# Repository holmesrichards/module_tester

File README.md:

Eurorack module tester.

This project is a test signal generator for Eurorack synth modules. It also provides frequency/clock measurement tools, and a +/12V and +5V power supply - making it a compact "all in one" box for powering and debugging a module.

Original developer: Emilie Gillet (emilie.o.gillet@gmail.com)

Forked from pichenettes' version and identical except:
- Eagle brd and sch files converted to XML (making possible import into KiCad)

The firmware is released under a GPL3.0 license. The PCB layouts and schematics are released under a Creative Commons cc-by-sa 3.0 license.

To build code and flash a blank 644p:
make -f module_tester/makefile bootstrap

this is a test

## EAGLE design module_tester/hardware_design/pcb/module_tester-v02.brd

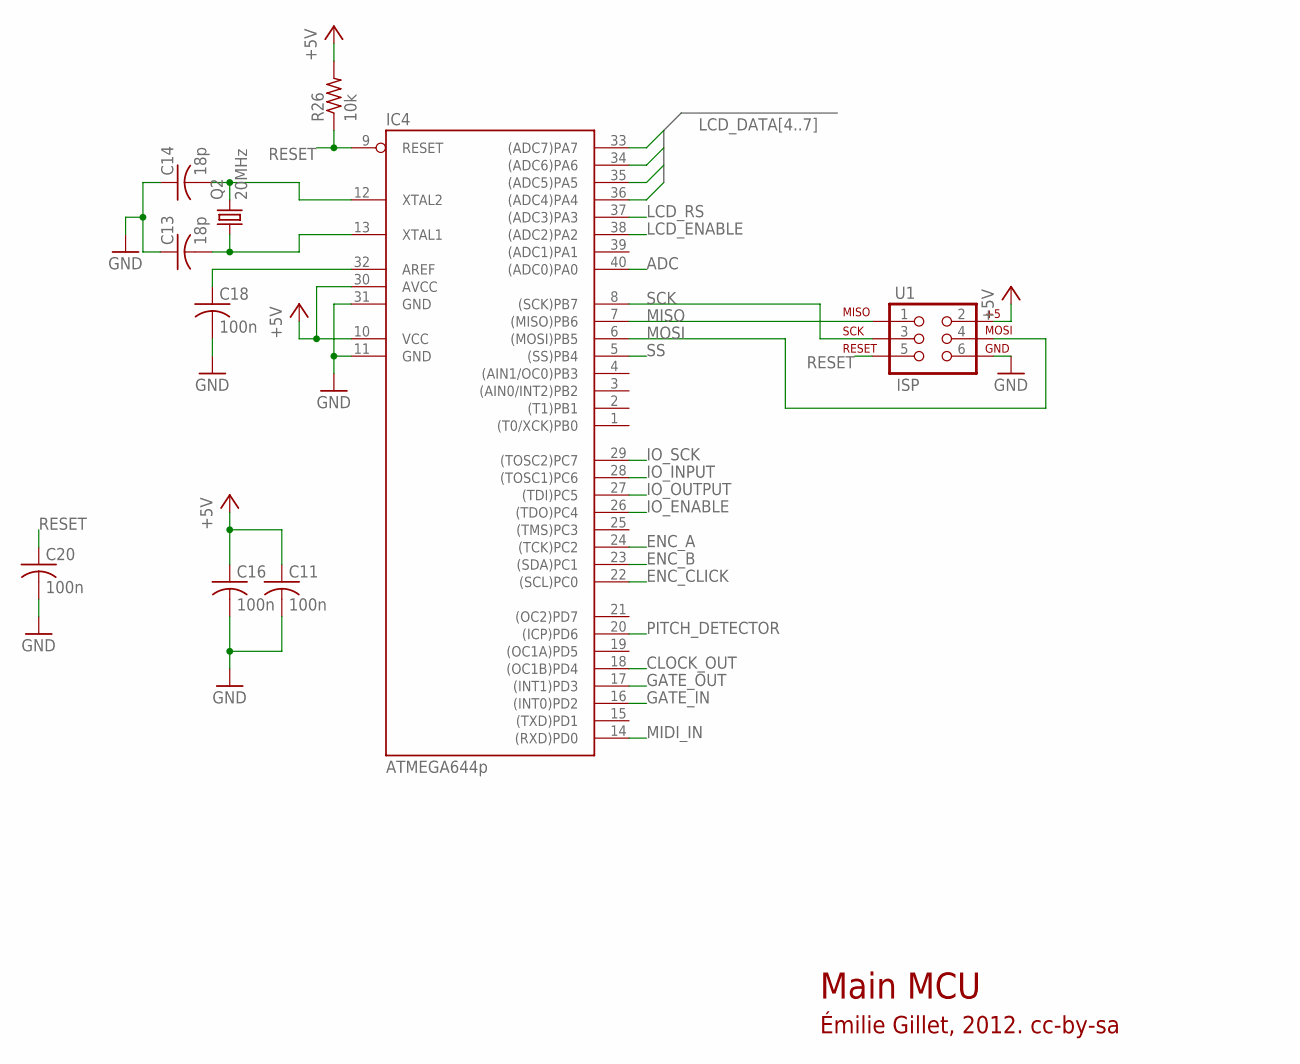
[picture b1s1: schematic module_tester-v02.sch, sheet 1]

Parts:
C11, C16, C18, C20: 100n; C025-025X050
C13, C14: 18p; C025-025X050
IC4: ATMEGA644p; DIL40
Q2: 20MHz; HC49U-V
R26: 10k; 0204/7
U1: ISP; 2X3

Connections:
+5V: C11.1, C16.1, IC4.10 (VCC), IC4.30 (AVCC), R26.2, U1.2; also elsewhere on the board
ADC: IC4.40 ((ADC0)PA0); also elsewhere on the board
CLOCK_OUT: IC4.18 ((OC1B)PD4); also elsewhere on the board
ENC_A: IC4.24 ((TCK)PC2); also elsewhere on the board
ENC_B: IC4.23 ((SDA)PC1); also elsewhere on the board
ENC_CLICK: IC4.22 ((SCL)PC0); also elsewhere on the board
GATE_IN: IC4.16 ((INT0)PD2); also elsewhere on the board
GATE_OUT: IC4.17 ((INT1)PD3); also elsewhere on the board
GND: C11.2, C13.1, C14.1, C16.2, C18.2, C20.2, IC4.11 (GND), IC4.31 (GND), U1.6; also elsewhere on the board
IO_ENABLE: IC4.26 ((TDO)PC4); also elsewhere on the board
IO_INPUT: IC4.28 ((TOSC1)PC6); also elsewhere on the board
IO_OUTPUT: IC4.27 ((TDI)PC5); also elsewhere on the board
IO_SCK: IC4.29 ((TOSC2)PC7); also elsewhere on the board
LCD_DATA4: IC4.36 ((ADC4)PA4); also elsewhere on the board
LCD_DATA5: IC4.35 ((ADC5)PA5); also elsewhere on the board
LCD_DATA6: IC4.34 ((ADC6)PA6); also elsewhere on the board
LCD_DATA7: IC4.33 ((ADC7)PA7); also elsewhere on the board
LCD_ENABLE: IC4.38 ((ADC2)PA2); also elsewhere on the board
LCD_RS: IC4.37 ((ADC3)PA3); also elsewhere on the board
MIDI_IN: IC4.14 ((RXD)PD0); also elsewhere on the board
MISO: IC4.7 ((MISO)PB6), U1.1
MOSI: IC4.6 ((MOSI)PB5), U1.4; also elsewhere on the board
unnamed: C18.1, IC4.32 (AREF)
unnamed: C13.2, IC4.13 (XTAL1), Q2.1
unnamed: C14.2, IC4.12 (XTAL2), Q2.2
PITCH_DETECTOR: IC4.20 ((ICP)PD6); also elsewhere on the board
RESET: C20.1, IC4.9 (RESET), R26.1, U1.5
SCK: IC4.8 ((SCK)PB7), U1.3; also elsewhere on the board
SS: IC4.5 ((SS)PB4); also elsewhere on the board

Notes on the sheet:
Main MCU
Émilie Gillet, 2012. cc-by-sa

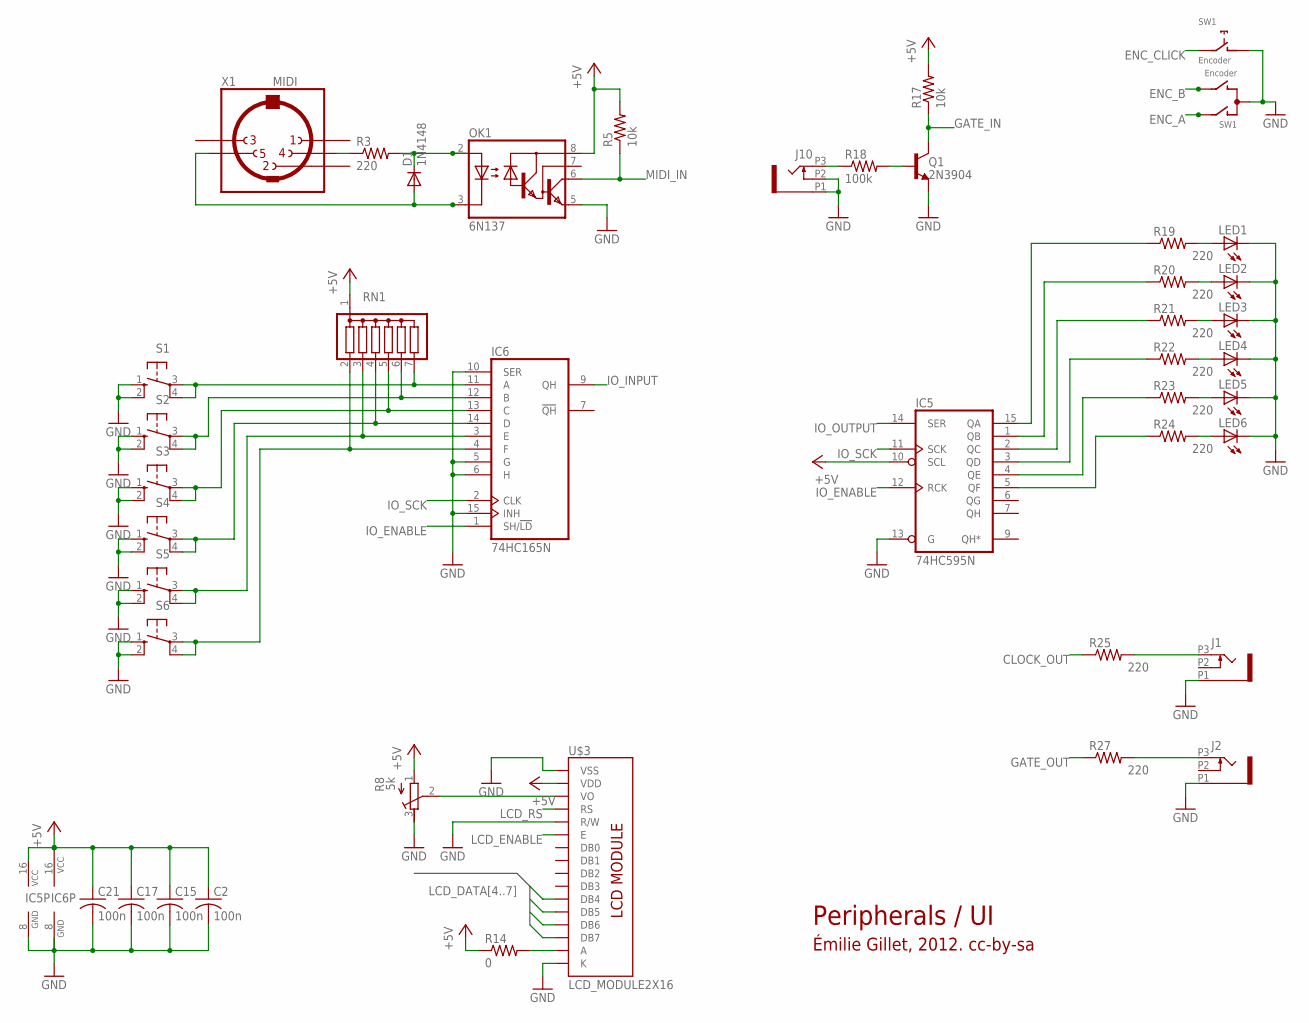
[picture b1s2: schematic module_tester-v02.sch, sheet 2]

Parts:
C2, C15, C17, C21: 100n; C025-025X050
D1: 1N4148; D-5
IC5: 74HC595N; DIL16
IC6: 74HC165N; DIL16
J1, J2, J10: PJ301_THONKICONN6; WQP_PJ_301M6
LED1, LED2, LED3, LED4, LED5, LED6: LED3MM
OK1: 6N137; DIL08
Q1: 2N3904; TO92-
R3, R19, R20, R21, R22, R23, R24, R25, R27: 220; 0204/7
R5, R17: 10k; 0204/7
R8: 5k; RTRIM3339P
R14: 0; 0204/7
R18: 100k; 0204/7
RN1: G06R; SIL7
S1, S2, S3, S4, S5, S6: 40-XX; B3F-40XX
SW1: Encoder; ALPS_EC12E_SW
U$3: LCD_MODULE2X16; LCD_MODULE_2X16
X1: MIDI; MAB5SH

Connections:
+5V: C2.1, C15.1, C17.1, C21.1, IC5.10 (SCL), IC5.16 (VCC), IC6.16 (VCC), OK1.8 (VCC), R5.2, R8.1 (E), R14.1, R17.2, RN1.1, U$3.2 (VDD); also elsewhere on the board
CLOCK_OUT: R25.1; also elsewhere on the board
ENC_A: SW1.A; also elsewhere on the board
ENC_B: SW1.B; also elsewhere on the board
ENC_CLICK: SW1.E (2); also elsewhere on the board
GATE_IN: Q1.1 (C), R17.1; also elsewhere on the board
GATE_OUT: R27.1; also elsewhere on the board
GND: C2.2, C15.2, C17.2, C21.2, IC5.8 (GND), IC5.13 (G), IC6.5 (G), IC6.6 (H), IC6.8 (GND), IC6.10 (SER), IC6.15 (INH), J1.P1 (1), J2.P1 (1), J10.P1 (1), J10.P2 (2), LED1.K (C), LED2.K (C), LED3.K (C), LED4.K (C), LED5.K (C), LED6.K (C), OK1.5 (GND), Q1.3 (E), R8.3 (A), S1.1 (S), S1.2 (S1), S2.1 (S), S2.2 (S1), S3.1 (S), S3.2 (S1), S4.1 (S), S4.2 (S1), S5.1 (S), S5.2 (S1), S6.1 (S), S6.2 (S1), SW1.C, SW1.D (1), U$3.1 (VSS), U$3.5 (R/W), U$3.16 (K); also elsewhere on the board
IO_ENABLE: IC5.12 (RCK), IC6.1 (SH/!LD); also elsewhere on the board
IO_INPUT: IC6.9 (QH); also elsewhere on the board
IO_OUTPUT: IC5.14 (SER); also elsewhere on the board
IO_SCK: IC5.11 (SCK), IC6.2 (CLK); also elsewhere on the board
LCD_DATA4: U$3.11 (DB4); also elsewhere on the board
LCD_DATA5: U$3.12 (DB5); also elsewhere on the board
LCD_DATA6: U$3.13 (DB6); also elsewhere on the board
LCD_DATA7: U$3.14 (DB7); also elsewhere on the board
LCD_ENABLE: U$3.6 (E); also elsewhere on the board
LCD_RS: U$3.4 (RS); also elsewhere on the board
MIDI_IN: OK1.6 (VO), R5.1; also elsewhere on the board
unnamed: IC5.2 (QC), R21.1
unnamed: IC5.4 (QE), R23.1
unnamed: LED5.A, R23.2
unnamed: J10.P3 (3), R18.1
unnamed: IC6.3 (E), RN1.3, S5.3, S5.4 (P1)
unnamed: J1.P3 (3), R25.2
unnamed: IC6.4 (F), RN1.2, S6.3, S6.4 (P1)
unnamed: IC6.14 (D), RN1.4, S4.3, S4.4 (P1)
unnamed: J2.P3 (3), R27.2
unnamed: R8.2 (S), U$3.3 (VO)
unnamed: LED6.A, R24.2
unnamed: IC5.5 (QF), R24.1
unnamed: IC6.11 (A), RN1.7, S1.3, S1.4 (P1)
unnamed: D1.C, OK1.2 (A), R3.2
unnamed: IC5.15 (QA), R19.1
unnamed: IC5.1 (QB), R20.1
unnamed: IC5.3 (QD), R22.1
unnamed: LED1.A, R19.2
unnamed: LED2.A, R20.2
unnamed: LED3.A, R21.2
unnamed: LED4.A, R22.2
unnamed: Q1.2 (B), R18.2
unnamed: R3.1, X1.4
unnamed: D1.A, OK1.3 (C), X1.5
unnamed: R14.2, U$3.15 (A)
unnamed: IC6.12 (B), RN1.6, S2.3, S2.4 (P1)
unnamed: IC6.13 (C), RN1.5, S3.3, S3.4 (P1)

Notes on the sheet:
Peripherals / UI
Émilie Gillet, 2012. cc-by-sa

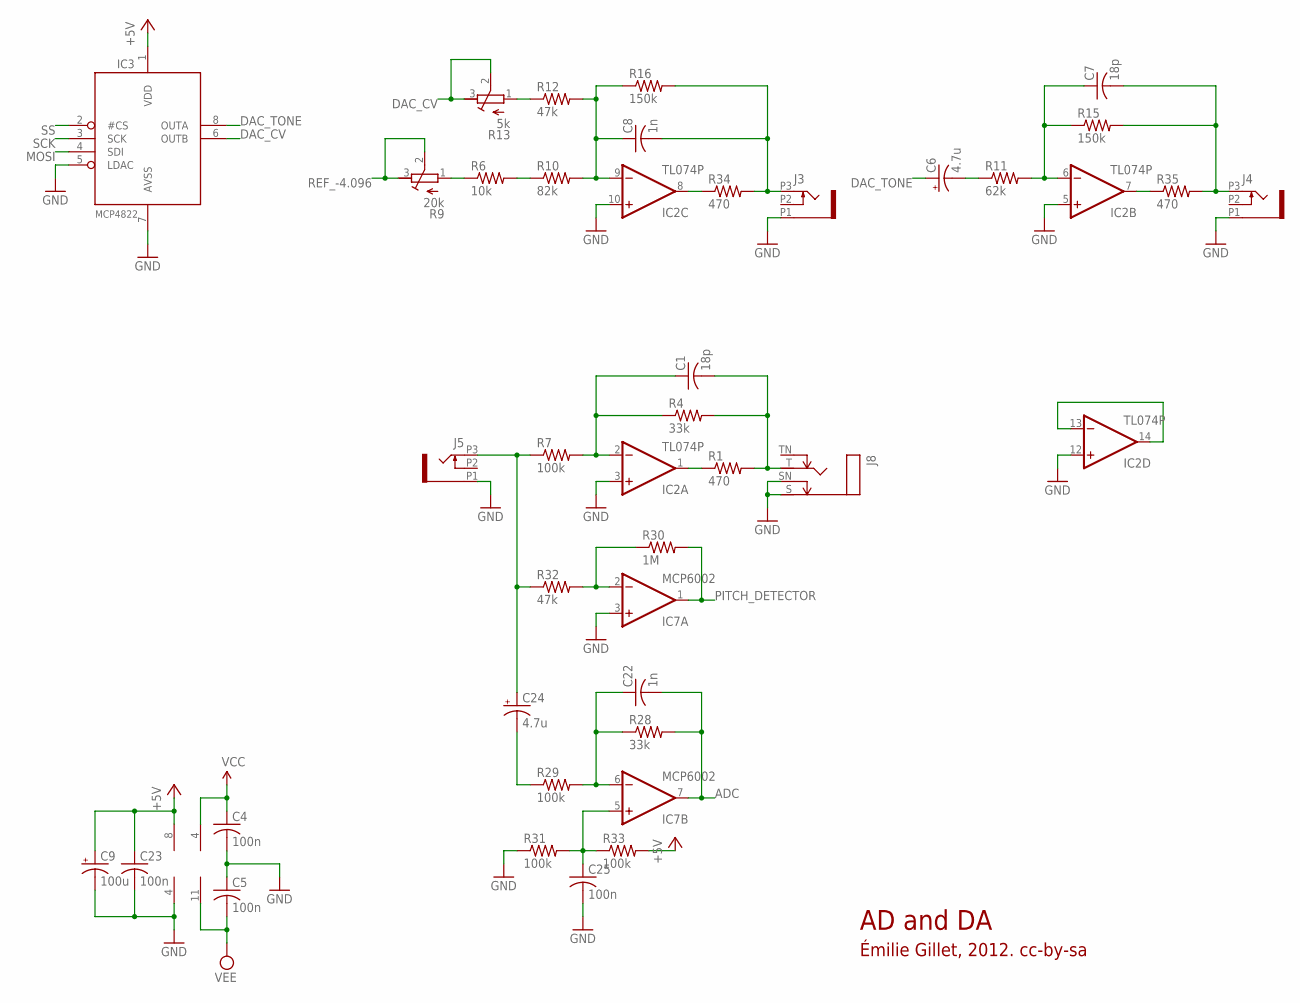
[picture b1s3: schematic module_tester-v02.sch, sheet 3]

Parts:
C1, C7: 18p; C025-025X050
C4, C5, C23, C25: 100n; C025-025X050
C6, C24: 4.7u; E2,5-6
C8, C22: 1n; C025-025X050
C9: 100u; E2,5-7
IC2: TL074P; DIL14
IC3: MCP4822; DIL08
IC7: MCP6002; DIL08
J3, J4, J5: PJ301_THONKICONN6; WQP_PJ_301M6
J8: MONOSWSLIM; NRJ4HF
R1, R34, R35: 470; 0204/7
R4, R28: 33k; 0204/7
R6: 10k; 0204/7
R7, R29, R31, R33: 100k; 0204/7
R9: 20k; RTRIM3296W
R10: 82k; 0204/7
R11: 62k; 0204/7
R12, R32: 47k; 0204/7
R13: 5k; RTRIM3296W
R15, R16: 150k; 0204/7
R30: 1M; 0204/7

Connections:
+5V: C9.+, C23.1, IC3.1 (VDD), IC7.8 (V+), R33.2; also elsewhere on the board
ADC: C22.2, IC7.7 (OUT), R28.2; also elsewhere on the board
DAC_CV: IC3.6 (OUTB), R13.2 (S), R13.3 (A)
DAC_TONE: C6.+, IC3.8 (OUTA)
GND: C4.2, C5.1, C9.-, C23.2, C25.2, IC2.3 (+IN), IC2.5 (+IN), IC2.10 (+IN), IC2.12 (+IN), IC3.5 (LDAC), IC3.7 (AVSS), IC7.3 (+IN), IC7.4 (V-), J3.P1 (1), J4.P1 (1), J5.P1 (1), J8.S, J8.SN, R31.1; also elsewhere on the board
MOSI: IC3.4 (SDI); also elsewhere on the board
unnamed: C24.+, J5.P3 (3), R7.1, R32.1
unnamed: IC2.8 (OUT), R34.1
unnamed: IC2.7 (OUT), R35.1
unnamed: C1.1, IC2.2 (-IN), R4.1, R7.2
unnamed: C1.2, J8.T, R1.2, R4.2
unnamed: C6.-, R11.1
unnamed: C7.1, IC2.6 (-IN), R11.2, R15.1
unnamed: C8.2, J3.P3 (3), R16.2, R34.2
unnamed: C8.1, IC2.9 (-IN), R10.2, R12.2, R16.1
unnamed: R12.1, R13.1 (E)
unnamed: R6.1, R9.1 (E)
unnamed: R6.2, R10.1
unnamed: C25.1, IC7.5 (+IN), R31.2, R33.1
unnamed: IC7.2 (-IN), R30.1, R32.2
unnamed: C22.1, IC7.6 (-IN), R28.1, R29.2
unnamed: C24.-, R29.1
unnamed: IC2.13 (-IN), IC2.14 (OUT)
unnamed: IC2.1 (OUT), R1.1
PITCH_DETECTOR: IC7.1 (OUT), R30.2; also elsewhere on the board
REF_-4.096: R9.2 (S), R9.3 (A); also elsewhere on the board
SCK: IC3.3 (SCK); also elsewhere on the board
SS: IC3.2 (#CS); also elsewhere on the board
TONE_OUT: C7.2, J4.P3 (3), R15.2, R35.2
VCC: C4.1, IC2.4 (V+); also elsewhere on the board
VEE: C5.2, IC2.11 (V-); also elsewhere on the board

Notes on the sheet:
AD and DA
Émilie Gillet, 2012. cc-by-sa

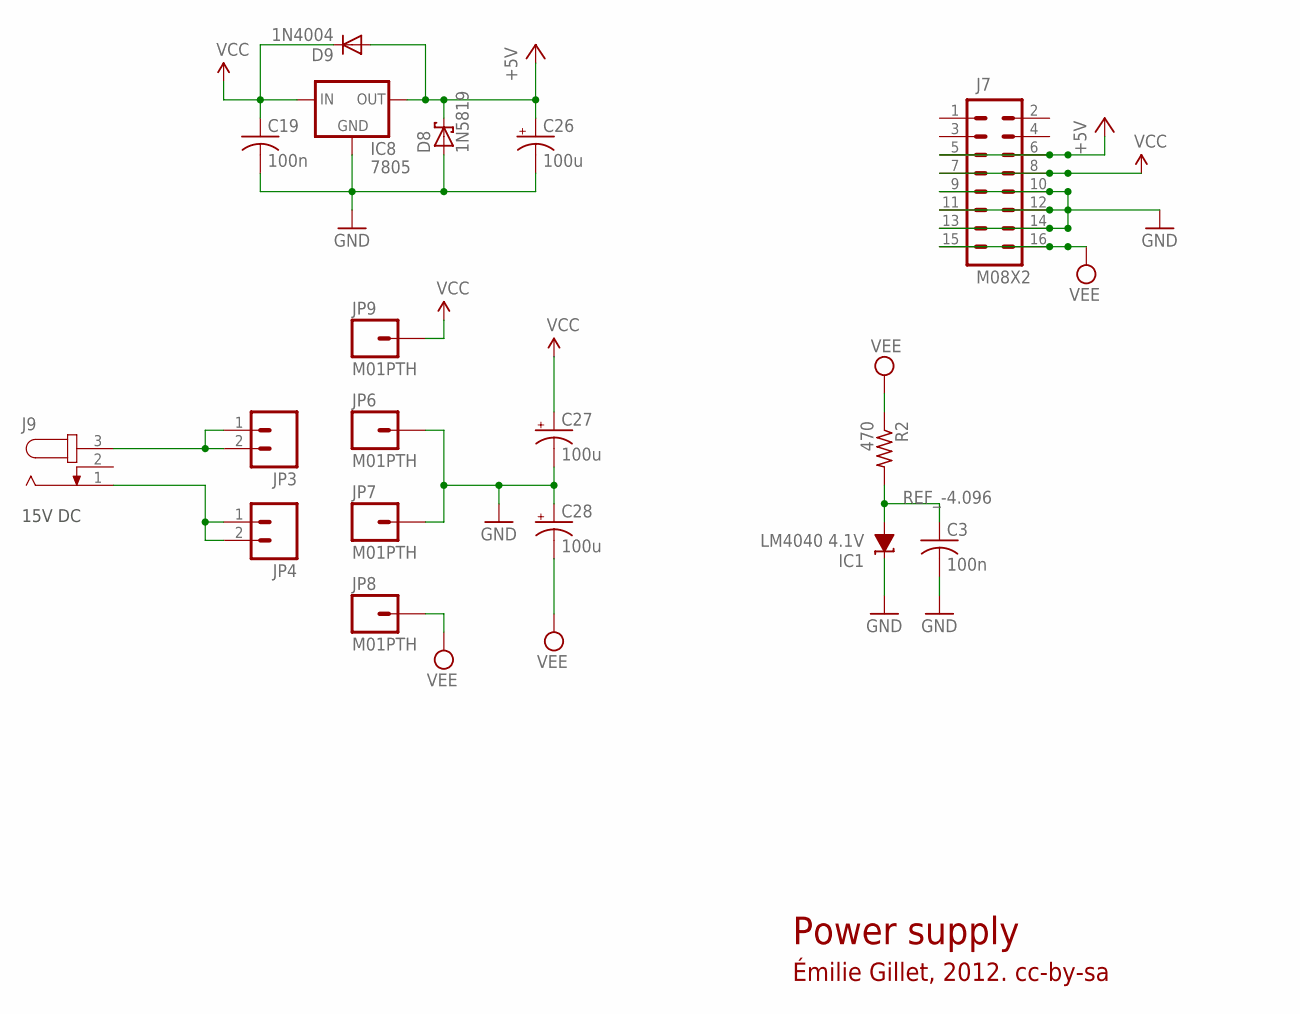
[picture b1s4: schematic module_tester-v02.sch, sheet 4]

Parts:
C3, C19: 100n; C025-025X050
C26, C27, C28: 100u; E2,5-7
D8: 1N5819; DO41-7.6
D9: 1N4004; DO41-10
IC1: LM4040 4.1V; LP_O-PBCY-W3
IC8: 7805; 78XXS
J7: M08X2; 2X8
J9: JACK-PLUG2; SPC4078_BIG_HOLES
JP3, JP4: M02PTH; 1X02
JP6, JP7, JP8, JP9: M01PTH; 1X01
R2: 470; 0204/7

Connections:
+5V: C26.+, D8.C, D9.A, IC8.OUT, J7.5, J7.6; also elsewhere on the board
GND: C3.2, C19.2, C26.-, C27.-, C28.+, D8.A, IC1.2 (C), IC8.GND, J7.9, J7.10, J7.11, J7.12, J7.13, J7.14, JP6.1, JP7.1; also elsewhere on the board
unnamed: J9.1, JP4.1, JP4.2
REF_-4.096: C3.1, IC1.3 (A), R2.2; also elsewhere on the board
TIP: J9.3, JP3.1, JP3.2
VCC: C19.1, C27.+, D9.C, IC8.IN, J7.7, J7.8, JP9.1; also elsewhere on the board
VEE: C28.-, J7.15, J7.16, JP8.1, R2.1; also elsewhere on the board

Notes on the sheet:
Power supply
Émilie Gillet, 2012. cc-by-sa
15V DC

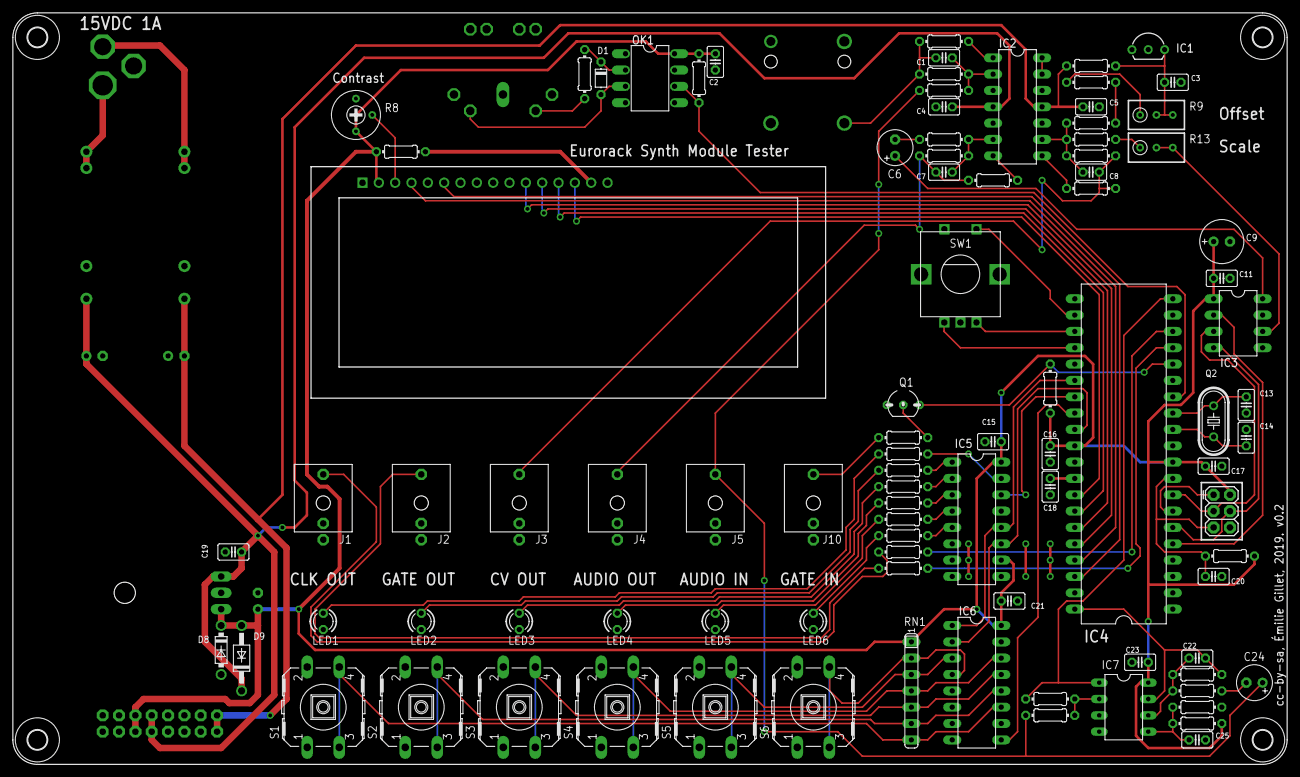
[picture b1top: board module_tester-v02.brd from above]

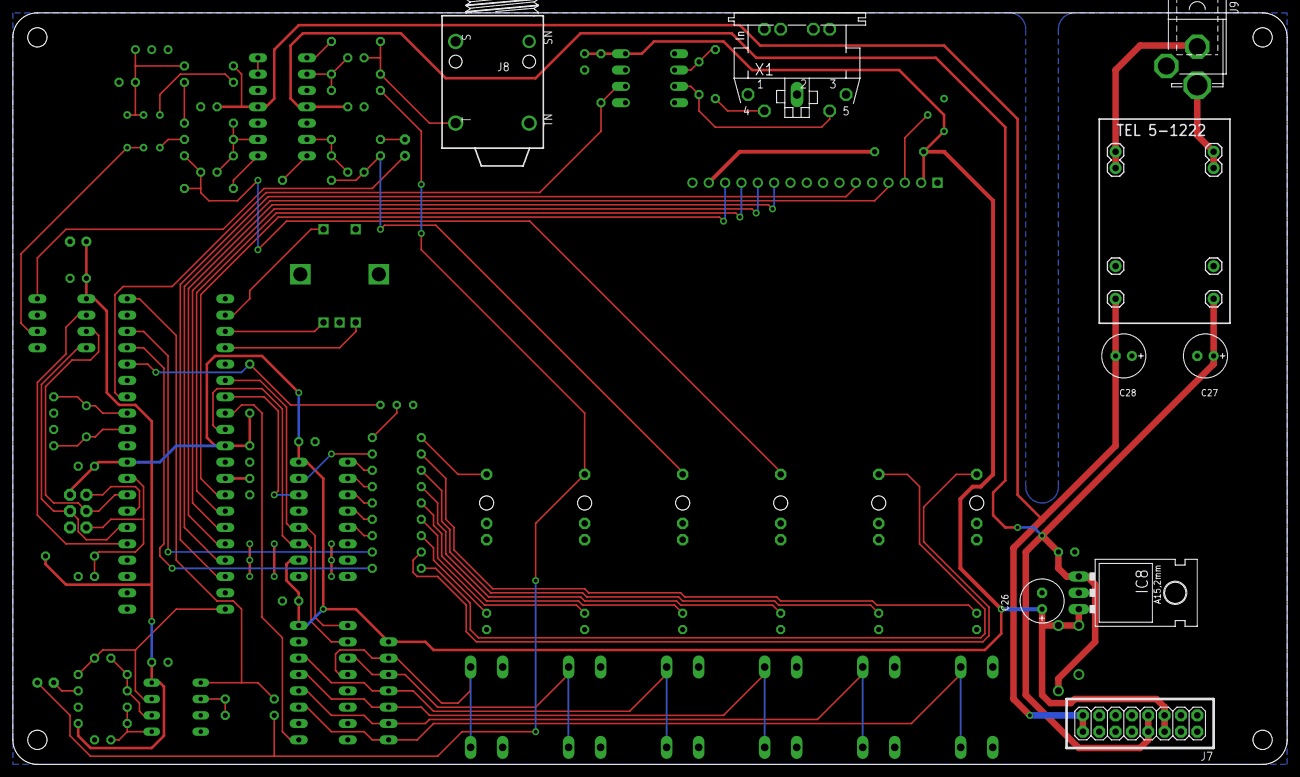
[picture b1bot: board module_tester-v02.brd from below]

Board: 2 copper layers, 198.1 x 116.8 mm, 111 parts (14 on the bottom side), 82 nets.

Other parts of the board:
U$1, U$2, U$5, U$6: 3,0

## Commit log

2020-03-23 Updated README for fork; XML conversions
2020-09-01 testing, testing...
2020-09-01 untest
